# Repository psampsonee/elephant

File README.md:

# Elephant

This project is intended to be a low-power audio player for a stuffed animal. The goal is to make a box that goes into a stuffed animal that takes up minimal space and lasts as long as possible on a single battery. The box should make an animal noise when its shaken, but only after some time has elapsed since the last time it has made a noise. The noise should be audible in a quiet room and should be immediately recognizable as a particular animal - in this case, an elephant. When the box has just been shaken, it will count - with very little power - a certain amount of time, then after that, wait to be shaken. Then, if you don't shake it, it should sit there, sipping very little power. When you do, it should make the animal noise within some amount of time (maybe a few fractions of a second).

## Power Budget / Battery Life

The board will have three main power states, corresponding to the three states of the state machine:

- Low-power
    - In this state, the STM32 is in standby mode. Everything but the backup domain - that is, the RTC and the backup registers - is powered off. Due to the quiescent currents of various devices during this state, it is expected that a little under 1 uA of current will draw from the main batteries.
- Buck Converter Off
    - The STM32 backup domain is powered only from its VBAT pin by the CR-2032 coin cell. Only the RTC and the backup registers are powered. This allows the STM32 to retain an accurate representation of the time. This will draw up to 2 uA from the CR-2032. However, testing will need to be done to verify this current consumption with the RTC in its particular configuration.
    - In this state, the buck converter becomes the predominate power sink for the main batteries, drawing 1 uA of current while shut down.
- Play Sound (highest power)
    - The microcontroller and DAC/amplifier (SSM2518) are both active, and the SSM2518 draws most of the current. This state will last for a few seconds, but contributes to a significant amount of the energy consumption of the main batteries. The LT-8640 will be supplying roughly 3.7W in this state and drawing 0.41A from the battery.

## State Machine

This firmware uses the Gang-of-Four State pattern: Elephant is the Context and each concrete state implements enter/toggle/exit. Each state is exposed via a singleton instance (no per-state heap allocations); any per-device data lives in the Elephant object. Interrupt service routines are kept tiny — they set flags or enqueue events — and the main loop/state handlers process those events and perform transitions, ensuring deterministic, non-blocking behavior. See notes in the README about concurrency (brief critical sections) and buffer sizing (samples vs bytes) (TODO).

The states in the state machine will correspond to each of the states mentioned in the **Power Budget / Battery Life** section above, with the following transition causes and tasks:

- Light Sleep
    - Upon waking up from standby, the firmware will detect why was reset (confirm entering standby), and why it woke (confirm RTC alarm) in main(). Once the STM32 is in this state, the STM32 will be in standby mode, corresponding to the "Low-power" power state.
    - Transitions to Deep Sleep when real time clock alarm fires. When the alarm fires, the STM32 briefly powers on completely to do the transition. During this transition, the microcontroller must save any data that needs to be retained (probably: last sound played (avoid repetition) and any state information needing to be retained) to spare backup registers, then pull the *GPIO_pwr_buck_off* pin low, triggering the 74AUP1G74 to clear, tying the LT8640 EN/UV pin low and causing it to power down.
- Deep Sleep
    - This state never sees a transition to another state in the code as the STM32 is completely powered off during it. Instead, the transition from this state occurs when the STM32 powers back on due to the LT8640 restoring power to the board. Corresponds to **Buck Converter Off**
    - "Transitions" to Play Sound when the tilt switch pulls the preload pin of the 74AUP1G74 low briefly, pulling Q high and turning the LT8640 back on.
- Play Sound
    - Upon powering on, the firmware will detect why was reset (POR), and why it woke (power restored) in main().  In this state, the STM32 will prepare the EEPROM for reading, then load data from the EEPROM in packets while playing a sound through the Audio object. Corresponds to the power state of the same name.
    - Transitions to Light Sleep when the Audio object completes playing a sound. During this transition, the STM32 sets an alarm 4 hours ahead of the current time to trigger it to wake up and transition into deep sleep.

## Choice of Components

### LT8640 Buck Converter

The LT8640 was chosen due to its high efficiency and ability to be turned off via the enable pin, which takes very little current to drive and allows the battery to be **practically** disconnected from the circuit (x nA is expected to leak while the LT8640 is turned off).

### STM32F401CCU Microcontroller

- Powerful enough to play intelligible audio
- Low-power options allow for RTC battery backup and external wakeups
- Nearly the same chip as on a "Black Pill" (For development)

### M95M04 EEPROM

- 4 Mbit is enough for several audio files (show calcs)
- Low Power
- 200 year data retention - not an SD card

### SSM2518 I2S DAC and amplifier

- Low quiescent current
- A one-chip solution to audio (maybe I dont need to say this in the final readme)
- Powerful enough to be heard at 2W per channel
-Very low noise

### LM66100 ideal diodes (power source OR-ing)

- Low quiescent (0.3uA) and leakage (max 600nA at operating temperature) currents
- Actively controlled PFET limits reverse-current to nanoamps. This is especially important for the coin cell to avoid damage, especially in high-temperature environments where a BAT54 could cause a failure in low-power mode.
- LM66100 ideal diodes were selected for power-source OR-ing due to their low quiescent current and low reverse leakage; reverse-current behavior into the coin cell is still being validated in simulation.

## Next Steps

## Risks and Unknowns

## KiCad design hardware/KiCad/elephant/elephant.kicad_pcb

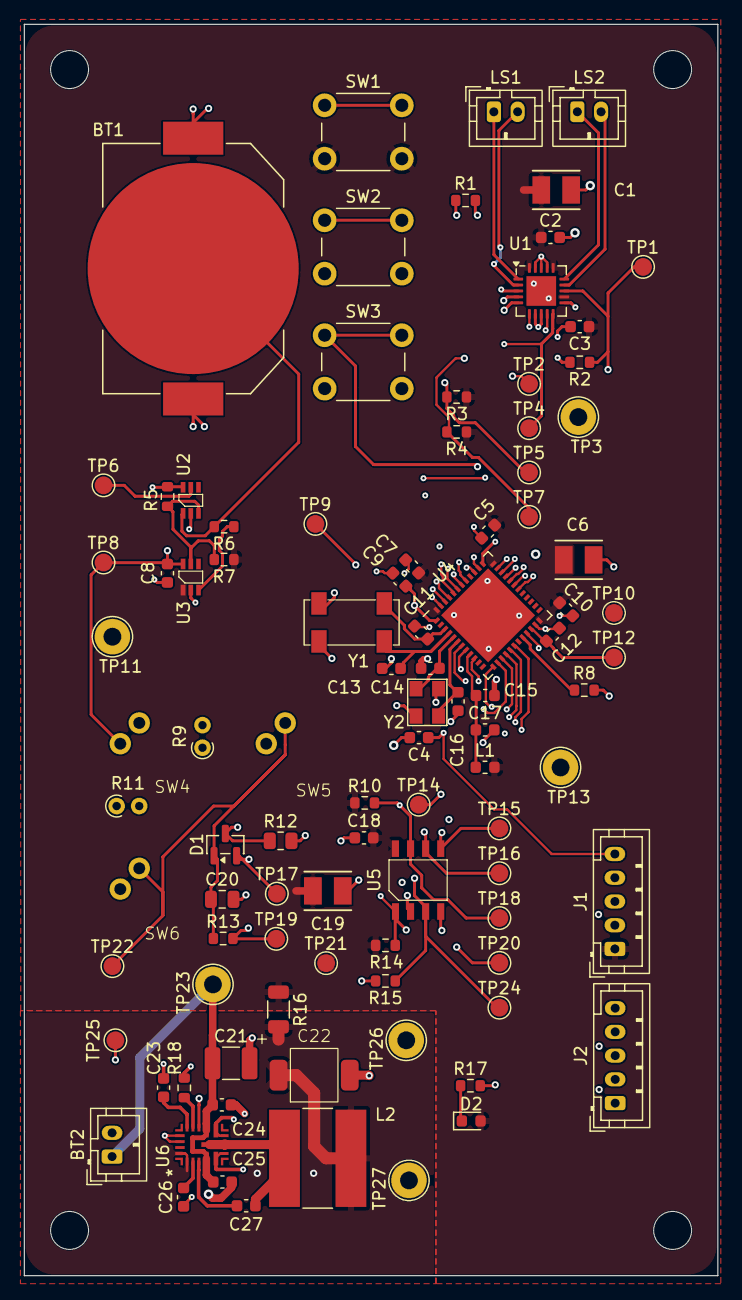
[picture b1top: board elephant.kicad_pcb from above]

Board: 4 copper layers, 58.4 x 105.4 mm, 101 parts (1 on the bottom side), 54 nets.

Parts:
BT1: Coin Cell; BAT_BK-912
BT2: 4x AAA Batteries; JST_PH_B2B-PH-K_1x02_P2.00mm_Vertical
C1, C6, C19: 4.7uF; CAP_TR3B_VIS
C2, C3, C4, C5, C7, C9, C10, C15, C18: 100nF; C_0603_1608Metric
C8, C17, C24, C25, C26, C27: 1uF; C_0603_1608Metric
C11, C13: 6pF; C_0603_1608Metric
C12: 4.7uF,<1Ω; C_0603_1608Metric
C14, C16: 10pF; C_0603_1608Metric
C20: 22nF; C_0805_2012Metric
C21: 10uF; C_1210_3225Metric_Pad1.33x2.70mm_HandSolder
C22: 100uF; Capacitor SMD 2917 (7343 Metric)
C23: 10nF; C_0603_1608Metric
D1: BAT54C; SOT-23
D2: LED; LED_0603_1608Metric
H1, H2, H3, H4: MountingHole; MountingHole_3.2mm_M3
Img1: Lou; LOGO
J1, J2: Conn_01x05_Pin; JST_PH_B5B-PH-K_1x05_P2.00mm_Vertical
L1: L_Ferrite; L_0603_1608Metric
L2: 2.2uH; L_Bourns-SRN8040_8x8.15mm
LS1, LS2: Speaker; JST_PH_B2B-PH-K_1x02_P2.00mm_Vertical
R1, R2, R6, R8, R10, R13, R14, R15: 10k; R_0603_1608Metric
R3, R4: 2k2; R_0603_1608Metric
R5: 1M; R_0603_1608Metric
R7: 2M; R_0603_1608Metric
R9, R11: 0 Ω; R_Axial_DIN0204_L3.6mm_D1.6mm_P1.90mm_Vertical
R12: 590k; R_0805_2012Metric
R16: 0 Ω; R_1206_3216Metric
R17: 330 Ω; R_0603_1608Metric
R18: 17.8k; R_0603_1608Metric
SW1, SW2, SW3: SW_MEC_5E; SW_PUSH_6mm
SW4, SW5, SW6: SW_TILT1; Tilt Switch
TP1, TP2, TP4, TP5, TP7, TP14, TP15, TP16, TP17, TP18, TP19, TP20, TP24: GPIO; TestPoint_Pad_D1.5mm
TP3, TP11, TP13, TP26: GND; TestPoint_Loop_D2.54mm_Drill1.5mm_Beaded
TP6: Backup_ST; TestPoint_Pad_D1.5mm
TP8, TP9: VBackup; TestPoint_Pad_D1.5mm
TP10, TP21: VBuckOut; TestPoint_Pad_D1.5mm
TP12: VCAP1; TestPoint_Pad_D1.5mm
TP22: Tilt; TestPoint_Pad_D1.5mm
TP23: BattMain; TestPoint_Loop_D2.54mm_Drill1.5mm_Beaded
TP25: BuckEn; TestPoint_Pad_D1.5mm
TP27: 3v3; TestPoint_Loop_D2.54mm_Drill1.5mm_Beaded
U1: SSM2518; QFN-20-1EP_4x4mm_P0.5mm_EP2.5x2.5mm
U2, U3: LM66100DCK; SC70-2.15mmX1.4mm
U4: STM32F401CCUx; UFQFPN-48_EP_7x7mm_Pitch0.5mm
U5: M95P32; 8-SO-4.9mmx3.9mm
U6: LT8640; UDCM_05-08-7030_ADI
Y1: 32.768kHz, 6pF, 70kΩ; ECX-306x
Y2: 25MHz, 8pF; ECS-33B2

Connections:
/ADC_sw_sense: R13.2, TP19.1 (1_1), U4.45 (PB8)
/BOOT0: R1.1, SW1.1, U4.44 (BOOT0)
/BOOT1: R8.1, U4.20 (PB2)
/GPIO_buck_en: D1.2, TP17.1 (1_1), U4.46 (PB9)
/I2C_SCL: R4.2, TP7.1 (1_1), U1.5 (SCL), U4.42 (PB6)
/I2C_SDA: R3.2, TP5.1 (1_1), U1.4 (SDA), U4.43 (PB7)
/I2S_bit_clock: U1.6 (MCLK), U4.39 (PB3)
/I2S_data: TP4.1 (1_1), U1.10 (SDATA), U4.41 (PB5)
/I2S_word_clock: TP2.1 (1_1), U1.9 (LRCLK), U4.38 (PA15)
/NRST: C4.1, J1.5, SW3.1, U4.7 (NRST)
/VREF+: C15.1, C17.1, L1.1, U4.9 (VREF+)
/WKUP: SW2.1, U4.10 (PA0)
/buck_en: D1.3, R12.1, TP25.1 (1_1), U6.14 (EN/UV)
/hold_eeprom: R10.2, TP18.1 (1_1), U4.18 (PB0), U5.7 (~HOLD)
/jtck_swclk: J1.3, U4.37 (PA14)
/jtms_swdio: J1.2, U4.34 (PA13)
/osc32_in: C11.2, U4.3 (PC14), Y1.1
/osc32_out: C13.2, U4.4 (PC15), Y1.4
/osc_in: C14.2, U4.5 (PH0), Y2.1
/osc_out: C16.2, U4.6 (PH1), Y2.3
/pwr_aud: R2.1, TP1.1 (1_1), U1.13 (SD), U4.21 (PB10)
/pwr_eeprom: R14.2, TP20.1 (1_1), U4.14 (PA4), U5.1 (~S)
/spi1_miso: TP14.1 (1_1), U4.16 (PA6), U5.2 (Q)
/spi1_mosi: TP15.1 (1_1), U4.17 (PA7), U5.5 (D)
/spi1_sck: TP16.1 (1_1), U4.15 (PA5), U5.6 (C)
/uart_cts: J2.3, U4.32 (PA11)
/uart_rts: J2.4, U4.33 (PA12)
/uart_rx: J2.2, U4.31 (PA10)
/uart_tx: J2.1, U4.30 (PA9)
/write_eeprom: R15.1, TP24.1 (1_1), U4.13 (PA3), U5.3 (~W)
GND: BT1.2 (-), BT2.2 (-), C1.2, C2.2, C3.2, C4.2, C5.2, C6.2, C7.2, C8.2, C9.2, C10.2, C11.1, C12.2, C13.1, C14.1, C15.2, C16.1, C17.2, C18.2, C19.2, C20.2, C21.2, C22.2, C23.2, C24.1, C25.2, C26.2, J1.4, J2.5, R1.2, R2.2, R8.2, R12.2, R15.2, R17.2, R18.2, SW2.2, SW3.2, TP3.1 (1_1), TP11.1 (1_1), TP13.1 (1_1), TP26.1 (1_1), U1.3 (ADDR), U1.7 (BCLK), U1.8 (GND), U1.11 (SAMOD), U1.17 (GND), U1.18 (GND), U1.19 (GND), U1.21 (GND), U2.2 (GND), U3.2 (GND), U4.8 (VSSA), U4.23 (VSS), U4.35 (VSS), U4.47 (VSS), U4.49 (EP), U5.4 (VSS), U6.6 (GND1), U6.7 (GND1), U6.10 (GND2), U6.11 (GND2), U6.17 (SYNC/MODE), U6.18 (GND), Y1.2 (G), Y1.3 (G), Y2.2 (G), Y2.4 (G)
unnamed: C27.2, L2.1, U6.8 (SW), U6.9 (SW), U6.21 (SW)
unnamed: D2.1 (K), R17.1
unnamed: R9.2, SW4.2 (B)
unnamed: R9.1, SW5.1 (A)
unnamed: C20.1, D1.1, R13.1, SW5.2 (B), SW6.2 (B), TP22.1 (1_1)
unnamed: R11.2, SW6.1 (A)
unnamed: LS1.1, U1.1 (OUTL+)
unnamed: LS1.2, U1.2 (OUTL-)
unnamed: LS2.1, U1.15 (OUTR+)
unnamed: LS2.2, U1.14 (OUTR-)
unnamed: TP6.1 (1_1), U2.5 (ST)
unnamed: R5.2, R7.2, U2.3 (~CE), U3.5 (ST)
unnamed: R6.1, U3.3 (~CE)
unnamed: C12.1, TP12.1 (1_1), U4.22 (VCAP1)
unnamed: C27.1, U6.3 (BST)
unnamed: C22.1, L2.2, R16.2, TP27.1 (1_1), U6.1 (Bias), U6.20 (Vout)
unnamed: C26.1, U6.2 (INTVcc)
unnamed: R18.1, U6.15 (RT)
unnamed: C23.1, U6.16 (TR/SS)
VBackup: C8.1, C9.1, R5.1, R11.1, SW4.1 (A), TP8.1 (1_1), TP9.1 (1_1), U2.6 (VOUT), U3.6 (VOUT), U4.1 (VBAT)
VBattMain: BT2.1 (+), C21.1, C24.2, C25.1, TP23.1 (1_1), U6.4 (Vin1), U6.13 (Vin2)
VBuckOut: C1.1, C2.1, C3.1, C5.1, C6.1, C7.1, C10.1, C18.1, C19.1, D2.2 (A), J1.1, L1.2, R3.1, R4.1, R7.1, R10.1, R14.1, R16.1, SW1.2, TP10.1 (1_1), TP21.1 (1_1), U1.12 (DVDD), U1.16 (PVDD), U1.20 (PVDD), U3.1 (VIN), U4.24 (VDD), U4.36 (VDD), U4.48 (VDD), U5.8 (VCC)
VCoin: BT1.1 (+), R6.2, U2.1 (VIN)

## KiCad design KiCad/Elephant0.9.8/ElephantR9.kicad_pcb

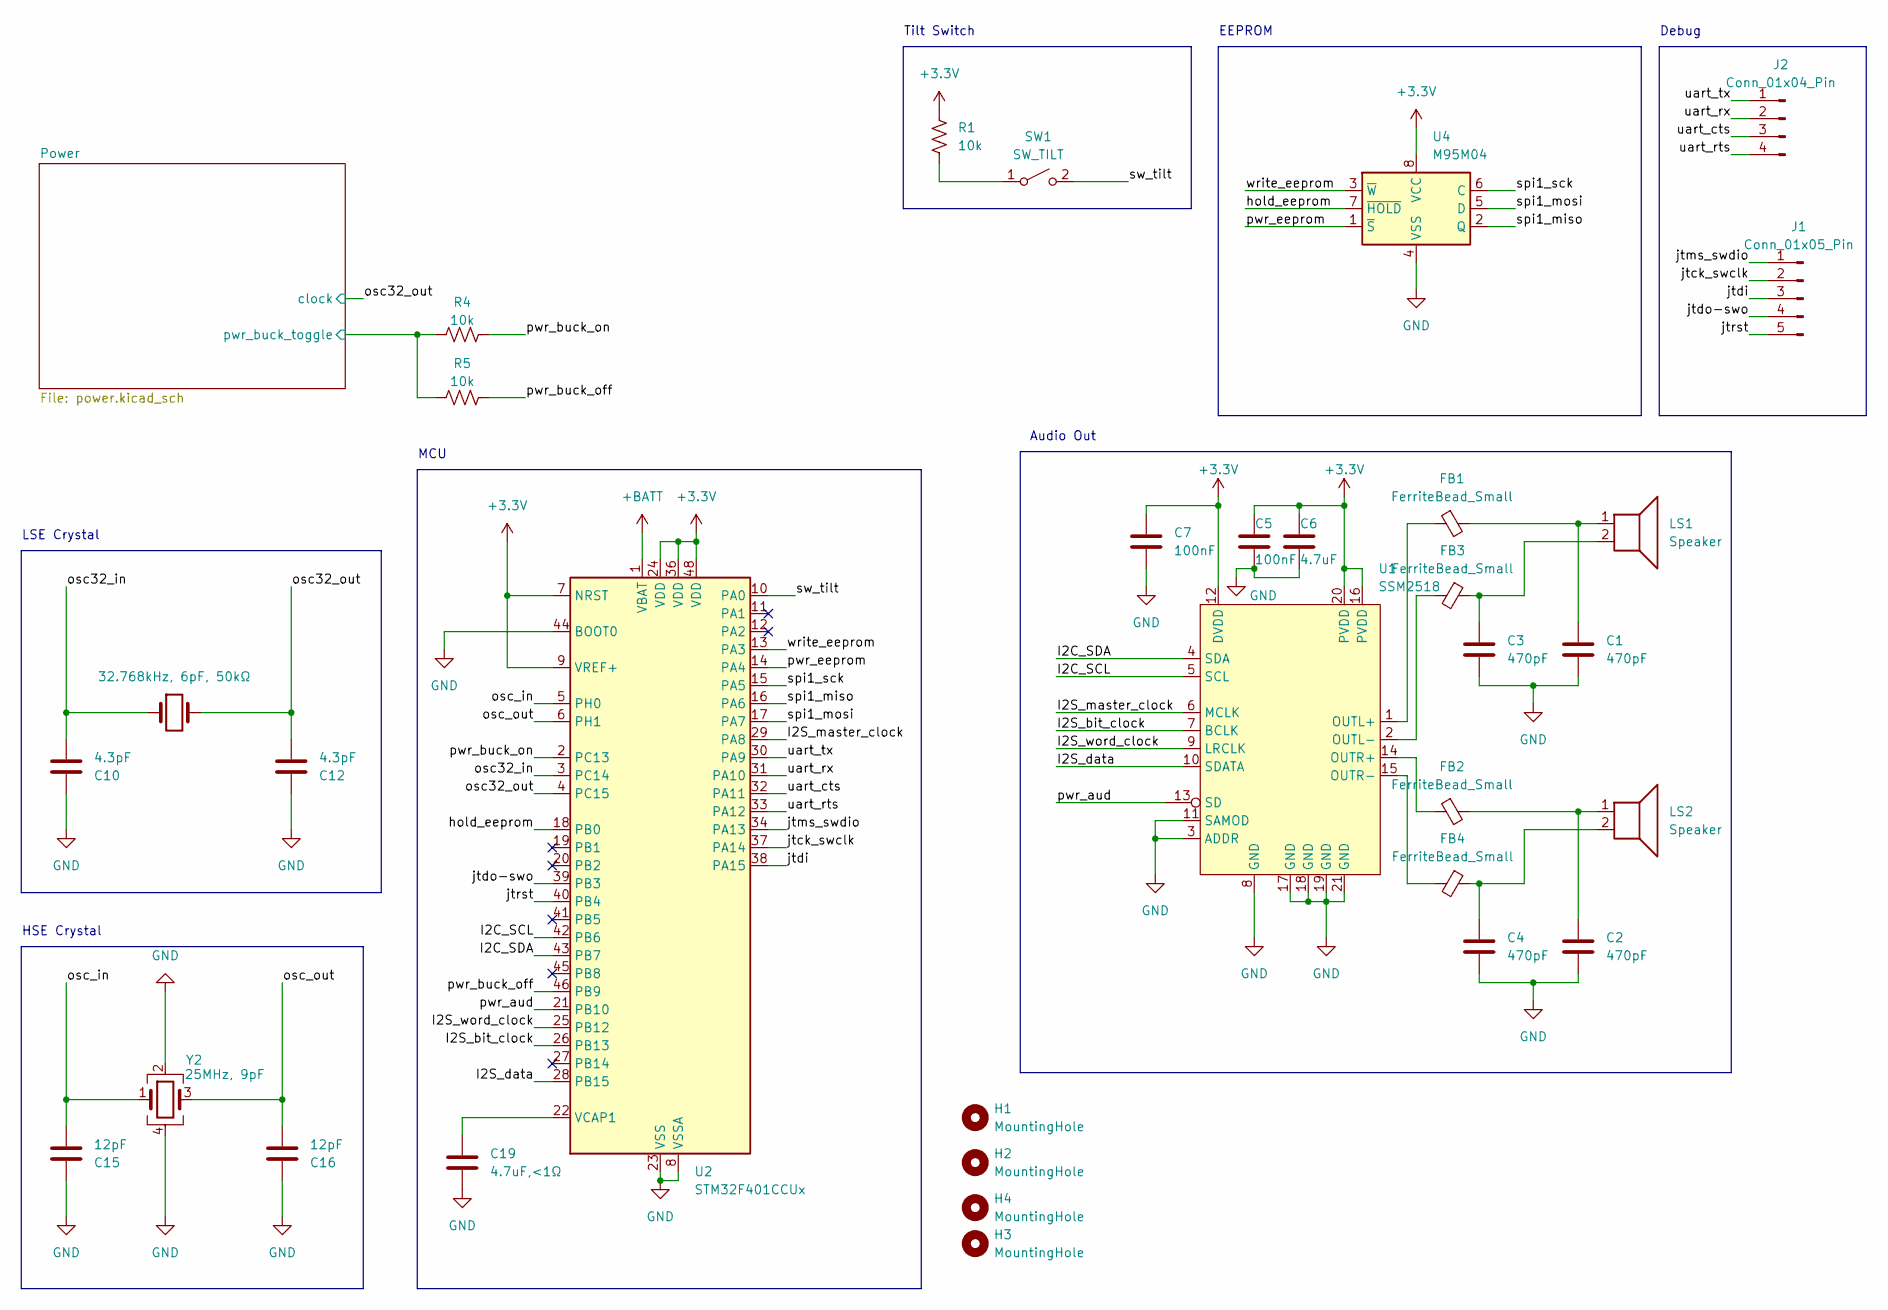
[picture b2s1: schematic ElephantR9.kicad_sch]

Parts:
C1, C2, C3, C4: 470pF; C_0603_1608Metric
C5, C7: 100nF; C_0603_1608Metric
C6: 4.7uF; C_0603_1608Metric
C10, C12: 4.3pF; C_0402_1005Metric
C15, C16: 12pF; C_0402_1005Metric
C19: 4.7uF,<1Ω; CP_Elec_4x5.4
FB1, FB2, FB3, FB4: FerriteBead_Small; L_0402_1005Metric
H1, H2, H3, H4: MountingHole; MountingHole_2.7mm_M2.5
J1: Conn_01x05_Pin; JST_PH_B5B-PH-K_1x05_P2.00mm_Vertical
J2: Conn_01x04_Pin; JST_PH_B4B-PH-K_1x04_P2.00mm_Vertical
LS1, LS2: Speaker; JST_PH_B2B-PH-K_1x02_P2.00mm_Vertical
R1, R4, R5: 10k; R_0603_1608Metric
SW1: SW_TILT; PinHeader_1x02_P2.54mm_Vertical
U1: SSM2518; QFN-20-1EP_4x4mm_P0.5mm_EP2.5x2.5mm
U2: STM32F401CCUx; QFN-48-1EP_7x7mm_P0.5mm_EP5.6x5.6mm
U4: M95M04; TSSOP-8_4.4x3mm_P0.65mm
Y1: 32.768kHz, 6pF, 50kΩ; Crystal_SMD_3215-2Pin_3.2x1.5mm
Y2: 25MHz, 9pF; Crystal_SMD_3225-4Pin_3.2x2.5mm

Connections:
+3.3V: C5.1, C6.1, C7.1, R1.1, U1.12 (DVDD), U1.16 (PVDD), U1.20 (PVDD), U2.7 (NRST), U2.9 (VREF+), U2.24 (VDD), U2.36 (VDD), U2.48 (VDD), U4.8 (VCC); also elsewhere on the board
+BATT: U2.1 (VBAT); also elsewhere on the board
/I2C_SCL: U1.5 (SCL), U2.42 (PB6)
/I2C_SDA: U1.4 (SDA), U2.43 (PB7)
/I2S_bit_clock: U1.7 (BCLK), U2.26 (PB13)
/I2S_data: U1.10 (SDATA), U2.28 (PB15)
/I2S_master_clock: U1.6 (MCLK), U2.29 (PA8)
/I2S_word_clock: U1.9 (LRCLK), U2.25 (PB12)
/Power/pwr_buck_toggle: R4.2, R5.2; also elsewhere on the board
/hold_eeprom: U2.18 (PB0), U4.7 (~HOLD)
/jtck_swclk: J1.2, U2.37 (PA14)
/jtdi: J1.3, U2.38 (PA15)
/jtdo-swo: J1.4, U2.39 (PB3)
/jtms_swdio: J1.1, U2.34 (PA13)
/jtrst: J1.5, U2.40 (PB4)
/osc32_in: C10.2, U2.3 (PC14), Y1.1
/osc32_out: C12.2, U2.4 (PC15), Y1.2; also elsewhere on the board
/osc_in: C15.2, U2.5 (PH0), Y2.1
/osc_out: C16.2, U2.6 (PH1), Y2.3
/pwr_aud: U1.13 (SD), U2.21 (PB10)
/pwr_buck_off: R5.1, U2.46 (PB9)
/pwr_buck_on: R4.1, U2.2 (PC13)
/pwr_eeprom: U2.14 (PA4), U4.1 (~S)
/spi1_miso: U2.16 (PA6), U4.2 (Q)
/spi1_mosi: U2.17 (PA7), U4.5 (D)
/spi1_sck: U2.15 (PA5), U4.6 (C)
/sw_tilt: SW1.2 (B), U2.10 (PA0)
/uart_cts: J2.3, U2.32 (PA11)
/uart_rts: J2.4, U2.33 (PA12)
/uart_rx: J2.2, U2.31 (PA10)
/uart_tx: J2.1, U2.30 (PA9)
/write_eeprom: U2.13 (PA3), U4.3 (~W)
GND: C1.2, C2.2, C3.2, C4.2, C5.2, C6.2, C7.2, C10.1, C12.1, C15.1, C16.1, C19.2, U1.3 (ADDR), U1.8 (GND), U1.11 (SAMOD), U1.17 (GND), U1.18 (GND), U1.19 (GND), U1.21 (GND), U2.8 (VSSA), U2.23 (VSS), U2.35 (VSS), U2.44 (BOOT0), U2.47 (VSS), U2.49 (VSS), U4.4 (VSS), Y2.2, Y2.4; also elsewhere on the board
unnamed: C1.1, FB1.2, LS1.1
unnamed: C2.1, FB2.2, LS2.1
unnamed: C3.1, FB3.1, LS1.2
unnamed: C4.1, FB4.1, LS2.2
unnamed: R1.2, SW1.1 (A)
unnamed: FB1.1, U1.1 (OUTL+)
unnamed: FB3.2, U1.2 (OUTL-)
unnamed: FB2.1, U1.14 (OUTR+)
unnamed: FB4.2, U1.15 (OUTR-)
unnamed: C19.1, U2.22 (VCAP1)

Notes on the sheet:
HSE Crystal
MCU
Debug
Audio Out
EEPROM
Tilt Switch
LSE Crystal

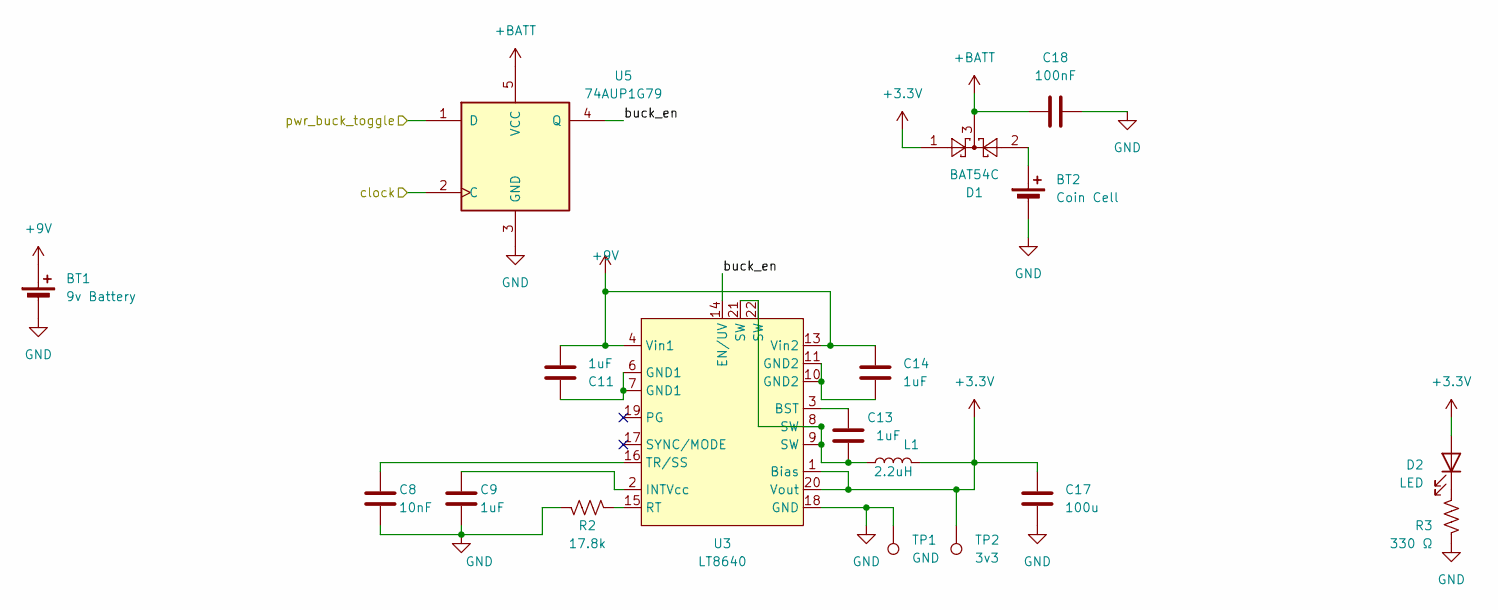
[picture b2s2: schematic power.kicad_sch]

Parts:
BT1: 9v Battery; JST_PH_B2B-PH-K_1x02_P2.00mm_Vertical
BT2: Coin Cell; BatteryHolder_Keystone_1057_1x2032
C8: 10nF; C_0603_1608Metric
C9, C11, C13, C14: 1uF; C_0603_1608Metric
C17: 100u; CP_Elec_6.3x5.3
C18: 100nF; C_0402_1005Metric
D1: BAT54C; SOT-23
D2: LED; LED_0603_1608Metric
L1: 2.2uH; L_Bourns-SRN8040_8x8.15mm
R2: 17.8k; R_0603_1608Metric
R3: 330 Ω; R_0603_1608Metric
TP1: GND; TestPoint_Pad_D1.0mm
TP2: 3v3; TestPoint_Pad_D1.0mm
U3: LT8640
U5: 74AUP1G79; SOT-23-5

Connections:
+3.3V: C17.1, D1.1, D2.2 (A), L1.2, TP2.1, U3.1 (Bias), U3.20 (Vout); also elsewhere on the board
+9V: BT1.1 (+), C11.2, C14.1, U3.4 (Vin1), U3.13 (Vin2)
+BATT: C18.1, D1.3, U5.5 (VCC); also elsewhere on the board
/Power/buck_en: U3.14 (EN/UV), U5.4 (Q)
/Power/pwr_buck_toggle: U5.1 (D); also elsewhere on the board
/osc32_out: U5.2 (C); also elsewhere on the board
GND: BT1.2 (-), BT2.2 (-), C8.2, C9.2, C17.2, C18.2, R2.2, R3.2, TP1.1, U3.18 (GND), U5.3 (GND); also elsewhere on the board
unnamed: BT2.1 (+), D1.2
unnamed: C11.1, U3.6 (GND1), U3.7 (GND1)
unnamed: C13.2, L1.1, U3.8 (SW), U3.9 (SW), U3.21 (SW), U3.22 (SW)
unnamed: C14.2, U3.10 (GND2), U3.11 (GND2)
unnamed: D2.1 (K), R3.1
unnamed: C13.1, U3.3 (BST)
unnamed: C9.1, U3.2 (INTVcc)
unnamed: R2.1, U3.15 (RT)
unnamed: C8.1, U3.16 (TR/SS)

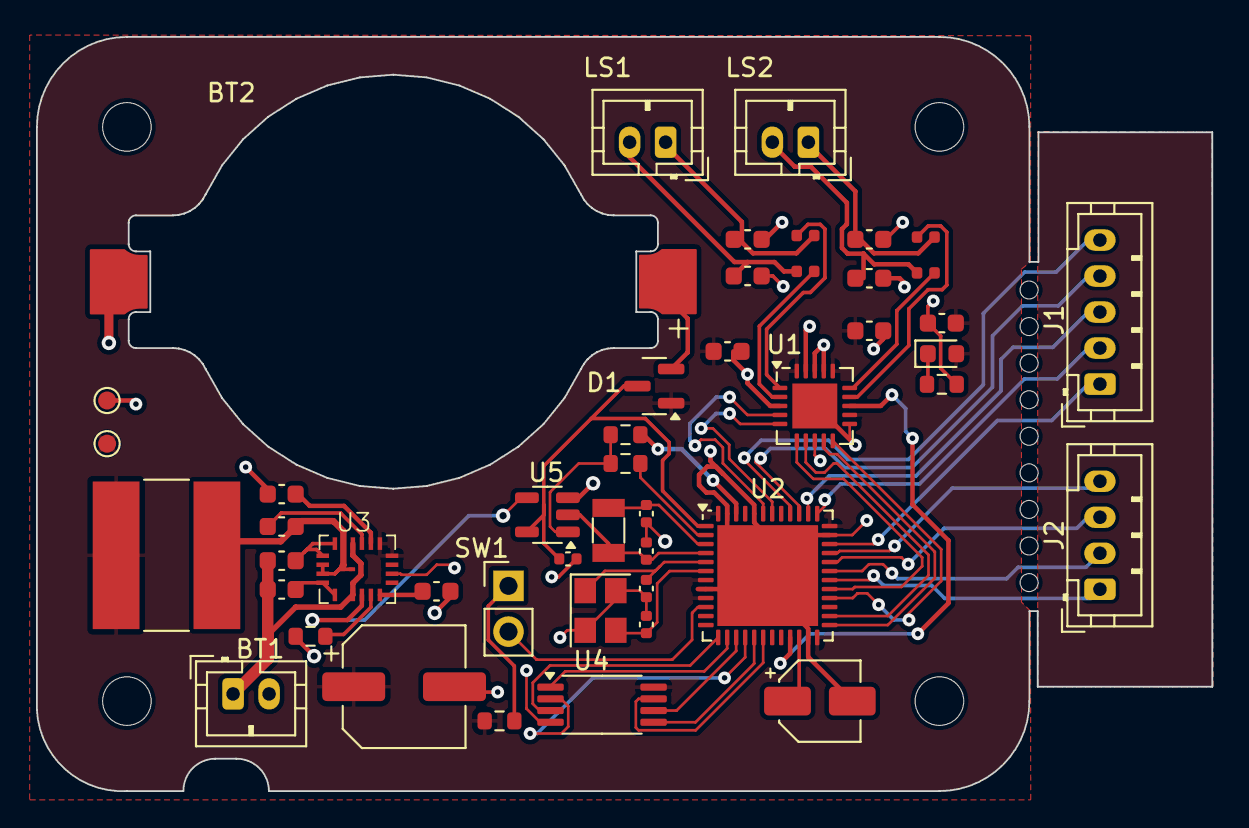
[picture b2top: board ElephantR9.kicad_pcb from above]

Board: 2 copper layers, 65.3 x 41.9 mm, 51 parts (0 on the bottom side), 54 nets.

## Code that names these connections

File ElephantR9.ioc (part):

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Mcu.Name=STM32F401C(B-C)Ux
Mcu.Package=UFQFPN48
Mcu.UserName=STM32F401CCUx
PA0-WKUP.GPIOParameters=GPIO_Label
PA0-WKUP.GPIO_Label=sw_tilt
PA0-WKUP.Mode=SYS_WakeUp0
PA0-WKUP.Signal=SYS_WKUP
PA1.GPIOParameters=GPIO_Label
PA1.GPIO_Label=ld_heartbeat
PA1.Signal=GPIO_Output
PA10.Mode=Asynchronous
PA10.Signal=USART1_RX
PA11.Mode=CTS_RTS
PA11.Signal=USART1_CTS
PA12.Mode=CTS_RTS
PA12.Signal=USART1_RTS
PA13.Mode=JTAG_5_pins
PA13.Signal=SYS_JTMS-SWDIO
PA14.Mode=JTAG_5_pins
PA14.Signal=SYS_JTCK-SWCLK
PA15.Mode=JTAG_5_pins
PA15.Signal=SYS_JTDI
PA2.GPIOParameters=GPIO_PuPd,GPIO_Label,GPIO_ModeDefaultEXTI
PA2.GPIO_Label=wakeup
PA2.GPIO_ModeDefaultEXTI=GPIO_MODE_IT_FALLING
PA2.GPIO_PuPd=GPIO_PULLUP
PA2.Signal=GPXTI2
PA3.GPIOParameters=GPIO_Label
PA3.GPIO_Label=pwr_eeprom
PA3.Signal=GPIO_Output
PA4.GPIOParameters=GPIO_Label
PA4.GPIO_Label=write_eeprom
PA4.Signal=GPIO_Output
PA5.Mode=Full_Duplex_Master
PA5.Signal=SPI1_SCK
PA6.Mode=Full_Duplex_Master
PA6.Signal=SPI1_MISO
PA7.Mode=Full_Duplex_Master
PA7.Signal=SPI1_MOSI
PA8.Mode=Clock-out-1
PA8.Signal=RCC_MCO_1
PA9.Mode=Asynchronous
PA9.Signal=USART1_TX
PB0.GPIOParameters=GPIO_Label
PB0.GPIO_Label=hold_eeprom
PB0.Signal=GPIO_Output
PB10.GPIOParameters=GPIO_Label
PB10.GPIO_Label=pwr_aud
PB10.Signal=GPIO_Output
PB12.Mode=Half_Duplex_Master
PB12.Signal=I2S2_WS
PB13.Mode=Half_Duplex_Master
PB13.Signal=I2S2_CK
PB15.Mode=Half_Duplex_Master
PB15.Signal=I2S2_SD
PB3.Mode=JTAG_5_pins
PB3.Signal=SYS_JTDO-SWO
PB4.Mode=JTAG_5_pins
PB4.Signal=SYS_JTRST
PB6.Mode=I2C
PB6.Signal=I2C1_SCL
PB7.Mode=I2C
PB7.Signal=I2C1_SDA
PC13-ANTI_TAMP.Mode=AlarmA_RoutedAF
PC13-ANTI_TAMP.Signal=RTC_AF1
PC14-OSC32_IN.Mode=LSE-External-Oscillator
PC14-OSC32_IN.Signal=RCC_OSC32_IN
PC15-OSC32_OUT.Mode=LSE-External-Oscillator
PC15-OSC32_OUT.Signal=RCC_OSC32_OUT
PH0\ -\ OSC_IN.Mode=HSE-External-Oscillator
PH0\ -\ OSC_IN.Signal=RCC_OSC_IN
PH1\ -\ OSC_OUT.Mode=HSE-External-Oscillator
PH1\ -\ OSC_OUT.Signal=RCC_OSC_OUT
RCC.HSE_VALUE=25000000
RCC.SYSCLKFreq_VALUE=84000000
RCC.SYSCLKSource=RCC_SYSCLKSOURCE_PLLCLK
board=custom

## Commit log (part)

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2026-02-01 Created TODO, JOURNAL
2026-02-01 Pushing recent changes.
2026-05-31 Added KiCad project files, LTSpice files, and documentation files.
2026-06-06 Restore manual STM32 build flash debug workflow
2026-06-10 Reading SD Card
    SD card to be used for temporary storage for audio-test
2026-06-28 Audio player software design started.
